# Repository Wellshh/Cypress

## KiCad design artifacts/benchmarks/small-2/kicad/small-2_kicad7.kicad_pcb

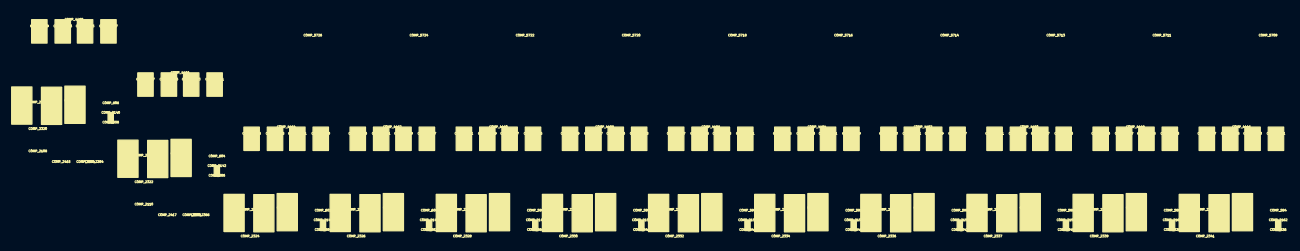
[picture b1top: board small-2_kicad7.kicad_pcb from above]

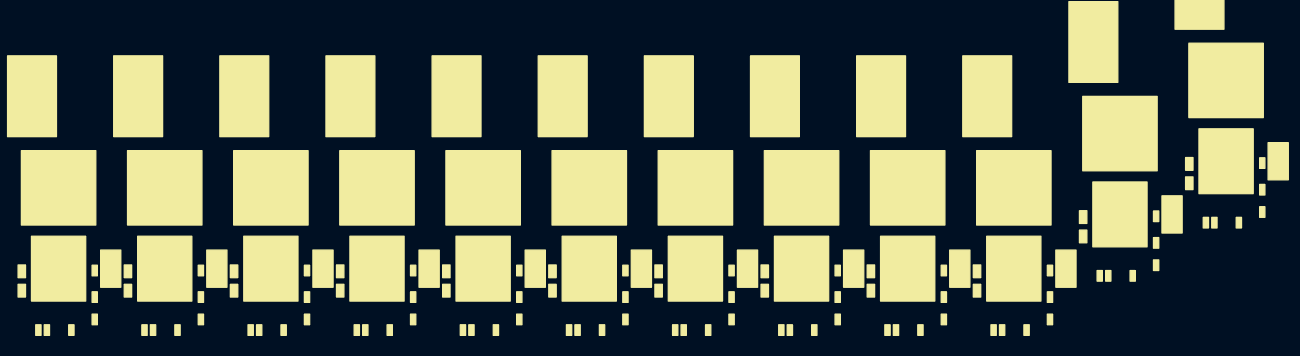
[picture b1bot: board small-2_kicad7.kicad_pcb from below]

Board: 2 copper layers, 240 parts (144 on the bottom side), 88 nets, no tracks yet.

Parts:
COMP_536: COMP_536; 032-1642-000
COMP_538: COMP_538; 032-1642-000
COMP_540: COMP_540; 032-1642-000
COMP_542: COMP_542; 032-1642-000
COMP_544: COMP_544; 032-1642-000
COMP_546: COMP_546; 032-1642-000
COMP_548: COMP_548; 032-1642-000
COMP_550: COMP_550; 032-1642-000
COMP_552: COMP_552; 032-1642-000
COMP_554: COMP_554; 032-1642-000
COMP_556: COMP_556; 032-1642-000
COMP_558: COMP_558; 032-1642-000
COMP_584: COMP_584; 032-1642-000
COMP_586: COMP_586; 032-1642-000
COMP_588: COMP_588; 032-1642-000
COMP_590: COMP_590; 032-1642-000
COMP_592: COMP_592; 032-1642-000
COMP_594: COMP_594; 032-1642-000
COMP_596: COMP_596; 032-1642-000
COMP_598: COMP_598; 032-1642-000
COMP_600: COMP_600; 032-1642-000
COMP_602: COMP_602; 032-1642-000
COMP_604: COMP_604; 032-1642-000
COMP_606: COMP_606; 032-1642-000
COMP_1898: COMP_1898; 032-1468-000
COMP_2108: COMP_2108; 032-1468-000
COMP_2110: COMP_2110; 032-1468-000
COMP_2112: COMP_2112; 032-1468-000
COMP_2114: COMP_2114; 032-1468-000
COMP_2116: COMP_2116; 032-1468-000
COMP_2118: COMP_2118; 032-1468-000
COMP_2120: COMP_2120; 032-1468-000
COMP_2121: COMP_2121; 032-0863-000
COMP_2123: COMP_2123; 032-1468-000
COMP_2125: COMP_2125; 032-1468-000
COMP_2127: COMP_2127; 032-1468-000
COMP_2129: COMP_2129; 032-1468-000
COMP_2140: COMP_2140; 195-3907-000
COMP_2142: COMP_2142; 195-3907-000
COMP_2144: COMP_2144; 195-3907-000
COMP_2146: COMP_2146; 195-3907-000
COMP_2148: COMP_2148; 195-3907-000
COMP_2150: COMP_2150; 195-3907-000
COMP_2152: COMP_2152; 195-3907-000
COMP_2154: COMP_2154; 195-3907-000
COMP_2156: COMP_2156; 195-3907-000
COMP_2158: COMP_2158; 195-3907-000
COMP_2160: COMP_2160; 195-3907-000
COMP_2162: COMP_2162; 195-3907-000
COMP_2184: COMP_2184; 195-3953-000
COMP_2186: COMP_2186; 195-3953-000
COMP_2188: COMP_2188; 195-3953-000
COMP_2190: COMP_2190; 195-3953-000
COMP_2192: COMP_2192; 195-3953-000
COMP_2194: COMP_2194; 195-3953-000
COMP_2196: COMP_2196; 195-3953-000
COMP_2198: COMP_2198; 195-3953-000
COMP_2200: COMP_2200; 195-3953-000
COMP_2202: COMP_2202; 195-3953-000
COMP_2204: COMP_2204; 195-3953-000
COMP_2206: COMP_2206; 195-3953-000
COMP_2288: COMP_2288; 032-0863-000
COMP_2290: COMP_2290; 032-0863-000
COMP_2292: COMP_2292; 032-0863-000
COMP_2296: COMP_2296; 032-0863-000
COMP_2298: COMP_2298; 032-0863-000
COMP_2300: COMP_2300; 032-0863-000
COMP_2302: COMP_2302; 032-0863-000
COMP_2304: COMP_2304; 032-0863-000
COMP_2306: COMP_2306; 032-0863-000
COMP_2308: COMP_2308; 032-0863-000
COMP_2310: COMP_2310; 032-0863-000
COMP_2320: COMP_2320; 032-0863-000
COMP_2322: COMP_2322; 032-0863-000
COMP_2324: COMP_2324; 032-0863-000
COMP_2326: COMP_2326; 032-0863-000
COMP_2328: COMP_2328; 032-0863-000
COMP_2330: COMP_2330; 032-0863-000
COMP_2332: COMP_2332; 032-0863-000
COMP_2334: COMP_2334; 032-0863-000
COMP_2336: COMP_2336; 032-0863-000
COMP_2337: COMP_2337; 032-0863-000
COMP_2339: COMP_2339; 032-0863-000
COMP_2341: COMP_2341; 032-0863-000
COMP_2351: COMP_2351; 195-2655-000
COMP_2384: COMP_2384; 195-2655-000
COMP_2386: COMP_2386; 195-2655-000
COMP_2388: COMP_2388; 195-2655-000
COMP_2390: COMP_2390; 195-2655-000
COMP_2392: COMP_2392; 195-2655-000
COMP_2394: COMP_2394; 195-2655-000
COMP_2396: COMP_2396; 195-2655-000
COMP_2398: COMP_2398; 195-2655-000
COMP_2400: COMP_2400; 195-2655-000
COMP_2402: COMP_2402; 195-2655-000
COMP_2404: COMP_2404; 195-2655-000
COMP_2406: COMP_2406; 195-2655-000
COMP_2407: COMP_2407; 195-2655-000
COMP_2415: COMP_2415; 195-2655-000
COMP_2417: COMP_2417; 195-2655-000
COMP_2419: COMP_2419; 195-2655-000
COMP_2421: COMP_2421; 195-2655-000
COMP_2423: COMP_2423; 195-2655-000
COMP_2425: COMP_2425; 195-2655-000
COMP_2427: COMP_2427; 195-2655-000
COMP_2429: COMP_2429; 195-2655-000
COMP_2431: COMP_2431; 195-2655-000
COMP_2435: COMP_2435; 195-2655-000
COMP_4062: COMP_4062; 032-2076-000
COMP_4064: COMP_4064; 032-2076-000
COMP_4066: COMP_4066; 032-2076-000
COMP_4068: COMP_4068; 032-2076-000
COMP_4070: COMP_4070; 032-2076-000
COMP_4072: COMP_4072; 032-2076-000
COMP_4074: COMP_4074; 032-2076-000
COMP_4076: COMP_4076; 032-2076-000
COMP_4078: COMP_4078; 032-2076-000
COMP_4080: COMP_4080; 032-2076-000
COMP_4082: COMP_4082; 032-2076-000
COMP_4084: COMP_4084; 032-2076-000
COMP_4094: COMP_4094; 032-2076-000
COMP_4096: COMP_4096; 032-2076-000
COMP_4098: COMP_4098; 032-2076-000
COMP_4100: COMP_4100; 032-2076-000
COMP_4102: COMP_4102; 032-2076-000
COMP_4104: COMP_4104; 032-2076-000
COMP_4106: COMP_4106; 032-2076-000
COMP_4108: COMP_4108; 032-2076-000
COMP_4110: COMP_4110; 032-2076-000
COMP_4112: COMP_4112; 032-2076-000
COMP_4114: COMP_4114; 032-2076-000
COMP_4116: COMP_4116; 032-2076-000
COMP_4126: COMP_4126; 032-2076-000
COMP_4128: COMP_4128; 032-2076-000
COMP_4130: COMP_4130; 032-2076-000
COMP_4132: COMP_4132; 032-2076-000
COMP_4134: COMP_4134; 032-2076-000
COMP_4136: COMP_4136; 032-2076-000
COMP_4138: COMP_4138; 032-2076-000
COMP_4140: COMP_4140; 032-2076-000
COMP_4142: COMP_4142; 032-2076-000
COMP_4144: COMP_4144; 032-2076-000
COMP_4146: COMP_4146; 032-2076-000
COMP_4148: COMP_4148; 032-2076-000
COMP_4158: COMP_4158; 032-2076-000
COMP_4160: COMP_4160; 032-2076-000
COMP_4162: COMP_4162; 032-2076-000
COMP_4164: COMP_4164; 032-2076-000
COMP_4166: COMP_4166; 032-2076-000
COMP_4168: COMP_4168; 032-2076-000
COMP_4170: COMP_4170; 032-2076-000
COMP_4172: COMP_4172; 032-2076-000
COMP_4174: COMP_4174; 032-2076-000
COMP_4176: COMP_4176; 032-2076-000
COMP_4178: COMP_4178; 032-2076-000
COMP_4180: COMP_4180; 032-2076-000
COMP_4308: COMP_4308; 316-0577-000
COMP_4310: COMP_4310; 316-0577-000
COMP_4312: COMP_4312; 316-0577-000
COMP_4314: COMP_4314; 316-0577-000
COMP_4316: COMP_4316; 316-0577-000
COMP_4318: COMP_4318; 316-0577-000
COMP_4320: COMP_4320; 316-0577-000
COMP_4322: COMP_4322; 316-0577-000
COMP_4324: COMP_4324; 316-0577-000
COMP_4326: COMP_4326; 316-0577-000
COMP_4328: COMP_4328; 316-0577-000
COMP_4330: COMP_4330; 316-0577-000
COMP_4446: COMP_4446; 130-1618-000
COMP_4448: COMP_4448; 130-1618-000
COMP_4450: COMP_4450; 130-1618-000
COMP_4452: COMP_4452; 130-1618-000
COMP_4454: COMP_4454; 130-1618-000
COMP_4456: COMP_4456; 130-1618-000
COMP_4458: COMP_4458; 130-1618-000
COMP_4460: COMP_4460; 130-1618-000
COMP_4462: COMP_4462; 130-1618-000
COMP_4464: COMP_4464; 130-1618-000
COMP_4466: COMP_4466; 130-1618-000
COMP_4468: COMP_4468; 130-1618-000
COMP_5321: COMP_5321; 032-0055-000
COMP_5323: COMP_5323; 032-0055-000
COMP_5325: COMP_5325; 032-0055-000
COMP_5327: COMP_5327; 032-0055-000
COMP_5329: COMP_5329; 032-0055-000
COMP_5331: COMP_5331; 032-0055-000
COMP_5333: COMP_5333; 032-0055-000
COMP_5335: COMP_5335; 032-0055-000
COMP_5337: COMP_5337; 032-0055-000
COMP_5339: COMP_5339; 032-0055-000
COMP_5341: COMP_5341; 032-0055-000
COMP_5343: COMP_5343; 032-0055-000
COMP_5353: COMP_5353; 032-0055-000
COMP_5355: COMP_5355; 032-0055-000
COMP_5357: COMP_5357; 032-0055-000
COMP_5359: COMP_5359; 032-0055-000
COMP_5361: COMP_5361; 032-0055-000
COMP_5363: COMP_5363; 032-0055-000
COMP_5365: COMP_5365; 032-0055-000
COMP_5367: COMP_5367; 032-0055-000
COMP_5369: COMP_5369; 032-0055-000
COMP_5371: COMP_5371; 032-0055-000
COMP_5373: COMP_5373; 032-0055-000
COMP_5375: COMP_5375; 032-0055-000
COMP_5385: COMP_5385; 032-0055-000
COMP_5387: COMP_5387; 032-0055-000
COMP_5389: COMP_5389; 032-0055-000
COMP_5391: COMP_5391; 032-0055-000
COMP_5393: COMP_5393; 032-0055-000
COMP_5395: COMP_5395; 032-0055-000
COMP_5397: COMP_5397; 032-0055-000
COMP_5399: COMP_5399; 032-0055-000
COMP_5401: COMP_5401; 032-0055-000
COMP_5403: COMP_5403; 032-0055-000
COMP_5405: COMP_5405; 032-0055-000
COMP_5407: COMP_5407; 032-0055-000
COMP_5417: COMP_5417; 032-0055-000
COMP_5419: COMP_5419; 032-0055-000
COMP_5421: COMP_5421; 032-0055-000
COMP_5423: COMP_5423; 032-0055-000
COMP_5425: COMP_5425; 032-0055-000
COMP_5427: COMP_5427; 032-0055-000
COMP_5429: COMP_5429; 032-0055-000
COMP_5431: COMP_5431; 032-0055-000
COMP_5433: COMP_5433; 032-0055-000
COMP_5435: COMP_5435; 032-0055-000
COMP_5437: COMP_5437; 032-0055-000
COMP_5439: COMP_5439; 032-0055-000
COMP_5709: COMP_5709; 032-1638-000
COMP_5711: COMP_5711; 032-1638-000
COMP_5713: COMP_5713; 032-1638-000
COMP_5714: COMP_5714; 032-1638-000
COMP_5716: COMP_5716; 032-1638-000
COMP_5718: COMP_5718; 032-1638-000
COMP_5720: COMP_5720; 032-1638-000
COMP_5722: COMP_5722; 032-1638-000
COMP_5724: COMP_5724; 032-1638-000
COMP_5726: COMP_5726; 032-1638-000
COMP_5728: COMP_5728; 032-1638-000
COMP_5730: COMP_5730; 032-1638-000

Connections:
NET_10: COMP_2121.1, COMP_2288.1, COMP_2290.1, COMP_2292.1, COMP_2296.1, COMP_2298.1, COMP_2300.1, COMP_2302.1, COMP_2304.1, COMP_2306.1, COMP_2308.1, COMP_2310.1, COMP_2320.1, COMP_2322.1, COMP_2324.1, COMP_2326.1, COMP_2328.1, COMP_2330.1, COMP_2332.1, COMP_2334.1, COMP_2336.1, COMP_2337.1, COMP_2339.1, COMP_2341.1, COMP_4062.1, COMP_4064.1, COMP_4066.1, COMP_4068.1, COMP_4070.1, COMP_4072.1, COMP_4074.1, COMP_4076.1, COMP_4078.1, COMP_4080.1, COMP_4082.1, COMP_4084.1, COMP_4094.1, COMP_4096.1, COMP_4098.1, COMP_4100.1, COMP_4102.1, COMP_4104.1, COMP_4106.1, COMP_4108.1, COMP_4110.1, COMP_4112.1, COMP_4114.1, COMP_4116.1, COMP_4126.1, COMP_4128.1, COMP_4130.1, COMP_4132.1, COMP_4134.1, COMP_4136.1, COMP_4138.1, COMP_4140.1, COMP_4142.1, COMP_4144.1, COMP_4146.1, COMP_4148.1, COMP_4158.1, COMP_4160.1, COMP_4162.1, COMP_4164.1, COMP_4166.1, COMP_4168.1, COMP_4170.1, COMP_4172.1, COMP_4174.1, COMP_4176.1, COMP_4178.1, COMP_4180.1, COMP_4308.25, COMP_4308.30, COMP_4310.25, COMP_4310.30, COMP_4312.25, COMP_4312.30, COMP_4314.25, COMP_4314.30, COMP_4316.25, COMP_4316.30, COMP_4318.25, COMP_4318.30, COMP_4320.25, COMP_4320.30, COMP_4322.25, COMP_4322.30, COMP_4324.25, COMP_4324.30, COMP_4326.25, COMP_4326.30, COMP_4328.25, COMP_4328.30, COMP_4330.25, COMP_4330.30
NET_373: COMP_2108.1, COMP_2415.2
NET_374: COMP_2110.1, COMP_2417.2
NET_375: COMP_2112.1, COMP_2419.2
NET_376: COMP_2114.1, COMP_2421.2
NET_377: COMP_2116.1, COMP_2423.2
NET_378: COMP_2118.1, COMP_2425.2
NET_380: COMP_2120.1, COMP_2427.2
NET_381: COMP_1898.1, COMP_2429.2
NET_382: COMP_2123.1, COMP_2431.2
NET_383: COMP_2127.1, COMP_2407.2
NET_384: COMP_2125.1, COMP_2351.2
NET_385: COMP_2129.1, COMP_2435.2
NET_420: COMP_2415.1, COMP_4308.33
NET_421: COMP_2417.1, COMP_4310.33
NET_422: COMP_2419.1, COMP_4312.33
NET_423: COMP_2421.1, COMP_4314.33
NET_424: COMP_2423.1, COMP_4316.33
NET_425: COMP_2425.1, COMP_4318.33
NET_427: COMP_2427.1, COMP_4320.33
NET_428: COMP_2429.1, COMP_4322.33
NET_429: COMP_2431.1, COMP_4324.33
NET_430: COMP_2407.1, COMP_4328.33
NET_431: COMP_2351.1, COMP_4326.33
NET_432: COMP_2435.1, COMP_4330.33
NET_468: COMP_2108.2, COMP_4308.32
NET_469: COMP_2110.2, COMP_4310.32
NET_470: COMP_2112.2, COMP_4312.32
NET_471: COMP_2114.2, COMP_4314.32
NET_472: COMP_2116.2, COMP_4316.32
NET_473: COMP_2118.2, COMP_4318.32
NET_475: COMP_2120.2, COMP_4320.32
NET_476: COMP_1898.2, COMP_4322.32
NET_477: COMP_2123.2, COMP_4324.32
NET_478: COMP_2127.2, COMP_4328.32
NET_479: COMP_2125.2, COMP_4326.32
NET_480: COMP_2129.2, COMP_4330.32
NET_516: COMP_4308.10, COMP_4308.11, COMP_4308.12, COMP_4308.13, COMP_4308.14, COMP_4308.15, COMP_4308.16, COMP_4308.17, COMP_4308.18, COMP_4308.19, COMP_4468.1
NET_517: COMP_4310.10, COMP_4310.11, COMP_4310.12, COMP_4310.13, COMP_4310.14, COMP_4310.15, COMP_4310.16, COMP_4310.17, COMP_4310.18, COMP_4310.19, COMP_4466.1
NET_518: COMP_4312.10, COMP_4312.11, COMP_4312.12, COMP_4312.13, COMP_4312.14, COMP_4312.15, COMP_4312.16, COMP_4312.17, COMP_4312.18, COMP_4312.19, COMP_4464.1
NET_519: COMP_4314.10, COMP_4314.11, COMP_4314.12, COMP_4314.13, COMP_4314.14, COMP_4314.15, COMP_4314.16, COMP_4314.17, COMP_4314.18, COMP_4314.19, COMP_4462.1
NET_520: COMP_4316.10, COMP_4316.11, COMP_4316.12, COMP_4316.13, COMP_4316.14, COMP_4316.15, COMP_4316.16, COMP_4316.17, COMP_4316.18, COMP_4316.19, COMP_4460.1
NET_521: COMP_4318.10, COMP_4318.11, COMP_4318.12, COMP_4318.13, COMP_4318.14, COMP_4318.15, COMP_4318.16, COMP_4318.17, COMP_4318.18, COMP_4318.19, COMP_4458.1
NET_523: COMP_4320.10, COMP_4320.11, COMP_4320.12, COMP_4320.13, COMP_4320.14, COMP_4320.15, COMP_4320.16, COMP_4320.17, COMP_4320.18, COMP_4320.19, COMP_4456.1
NET_524: COMP_4322.10, COMP_4322.11, COMP_4322.12, COMP_4322.13, COMP_4322.14, COMP_4322.15, COMP_4322.16, COMP_4322.17, COMP_4322.18, COMP_4322.19, COMP_4454.1
NET_525: COMP_4324.10, COMP_4324.11, COMP_4324.12, COMP_4324.13, COMP_4324.14, COMP_4324.15, COMP_4324.16, COMP_4324.17, COMP_4324.18, COMP_4324.19, COMP_4452.1
NET_526: COMP_4328.10, COMP_4328.11, COMP_4328.12, COMP_4328.13, COMP_4328.14, COMP_4328.15, COMP_4328.16, COMP_4328.17, COMP_4328.18, COMP_4328.19, COMP_4448.1
NET_527: COMP_4326.10, COMP_4326.11, COMP_4326.12, COMP_4326.13, COMP_4326.14, COMP_4326.15, COMP_4326.16, COMP_4326.17, COMP_4326.18, COMP_4326.19, COMP_4450.1
NET_528: COMP_4330.10, COMP_4330.11, COMP_4330.12, COMP_4330.13, COMP_4330.14, COMP_4330.15, COMP_4330.16, COMP_4330.17, COMP_4330.18, COMP_4330.19, COMP_4446.1
NET_5240: COMP_2184.2, COMP_4308.35
NET_5241: COMP_2186.2, COMP_4310.35
NET_5242: COMP_2188.2, COMP_4312.35
NET_5243: COMP_2190.2, COMP_4314.35
NET_5244: COMP_2192.2, COMP_4316.35
NET_5245: COMP_2194.2, COMP_4318.35
NET_5247: COMP_2196.2, COMP_4320.35
NET_5248: COMP_2198.2, COMP_4322.35
NET_5249: COMP_2200.2, COMP_4324.35
NET_5250: COMP_2204.2, COMP_4328.35
NET_5251: COMP_2202.2, COMP_4326.35
NET_5252: COMP_2206.2, COMP_4330.35
NET_5288: COMP_2384.2, COMP_4308.36
NET_5289: COMP_2386.2, COMP_4310.36
NET_5290: COMP_2388.2, COMP_4312.36
NET_5291: COMP_2390.2, COMP_4314.36
NET_5292: COMP_2392.2, COMP_4316.36
NET_5293: COMP_2394.2, COMP_4318.36
NET_5295: COMP_2396.2, COMP_4320.36
NET_5296: COMP_2398.2, COMP_4322.36
NET_5297: COMP_2400.2, COMP_4324.36
NET_5298: COMP_2404.2, COMP_4328.36
NET_5299: COMP_2402.2, COMP_4326.36
NET_5300: COMP_2406.2, COMP_4330.36
NET_5336: COMP_558.1, COMP_2140.2, COMP_2184.1, COMP_4308.3
NET_5337: COMP_556.1, COMP_2142.2, COMP_2186.1, COMP_4310.3
NET_5338: COMP_554.1, COMP_2144.2, COMP_2188.1, COMP_4312.3
NET_5339: COMP_552.1, COMP_2146.2, COMP_2190.1, COMP_4314.3
NET_5340: COMP_550.1, COMP_2148.2, COMP_2192.1, COMP_4316.3
NET_5341: COMP_548.1, COMP_2150.2, COMP_2194.1, COMP_4318.3
NET_5343: COMP_546.1, COMP_2152.2, COMP_2196.1, COMP_4320.3
NET_5344: COMP_544.1, COMP_2154.2, COMP_2198.1, COMP_4322.3
NET_5345: COMP_542.1, COMP_2156.2, COMP_2200.1, COMP_4324.3
NET_5346: COMP_538.1, COMP_2160.2, COMP_2204.1, COMP_4328.3
NET_5347: COMP_540.1, COMP_2158.2, COMP_2202.1, COMP_4326.3
NET_5348: COMP_536.1, COMP_2162.2, COMP_2206.1, COMP_4330.3
NET_5522: COMP_2384.1, COMP_2386.1, COMP_2388.1, COMP_2390.1, COMP_2392.1, COMP_2394.1, COMP_2396.1, COMP_2398.1, COMP_2400.1, COMP_2402.1, COMP_2404.1, COMP_2406.1
NET_5566: COMP_4446.2, COMP_4448.2, COMP_4450.2, COMP_4452.2, COMP_4454.2, COMP_4456.2, COMP_4458.2, COMP_4460.2, COMP_4462.2, COMP_4464.2, COMP_4466.2, COMP_4468.2, COMP_5321.1, COMP_5323.1, COMP_5325.1, COMP_5327.1, COMP_5329.1, COMP_5331.1, COMP_5333.1, COMP_5335.1, COMP_5337.1, COMP_5339.1, COMP_5341.1, COMP_5343.1, COMP_5353.1, COMP_5355.1, COMP_5357.1, COMP_5359.1, COMP_5361.1, COMP_5363.1, COMP_5365.1, COMP_5367.1, COMP_5369.1, COMP_5371.1, COMP_5373.1, COMP_5375.1, COMP_5385.1, COMP_5387.1, COMP_5389.1, COMP_5391.1, COMP_5393.1, COMP_5395.1, COMP_5397.1, COMP_5399.1, COMP_5401.1, COMP_5403.1, COMP_5405.1, COMP_5407.1, COMP_5417.1, COMP_5419.1, COMP_5421.1, COMP_5423.1, COMP_5425.1, COMP_5427.1, COMP_5429.1, COMP_5431.1, COMP_5433.1, COMP_5435.1, COMP_5437.1, COMP_5439.1, COMP_5709.1, COMP_5711.1, COMP_5713.1, COMP_5714.1, COMP_5716.1, COMP_5718.1, COMP_5720.1, COMP_5722.1, COMP_5724.1, COMP_5726.1, COMP_5728.1, COMP_5730.1
NET_5567: COMP_584.1, COMP_586.1, COMP_588.1, COMP_590.1, COMP_592.1, COMP_594.1, COMP_596.1, COMP_598.1, COMP_600.1, COMP_602.1, COMP_604.1, COMP_606.1, COMP_2140.1, COMP_2142.1, COMP_2144.1, COMP_2146.1, COMP_2148.1, COMP_2150.1, COMP_2152.1, COMP_2154.1, COMP_2156.1, COMP_2158.1, COMP_2160.1, COMP_2162.1, COMP_4308.4, COMP_4310.4, COMP_4312.4, COMP_4314.4, COMP_4316.4, COMP_4318.4, COMP_4320.4, COMP_4322.4, COMP_4324.4, COMP_4326.4, COMP_4328.4, COMP_4330.4

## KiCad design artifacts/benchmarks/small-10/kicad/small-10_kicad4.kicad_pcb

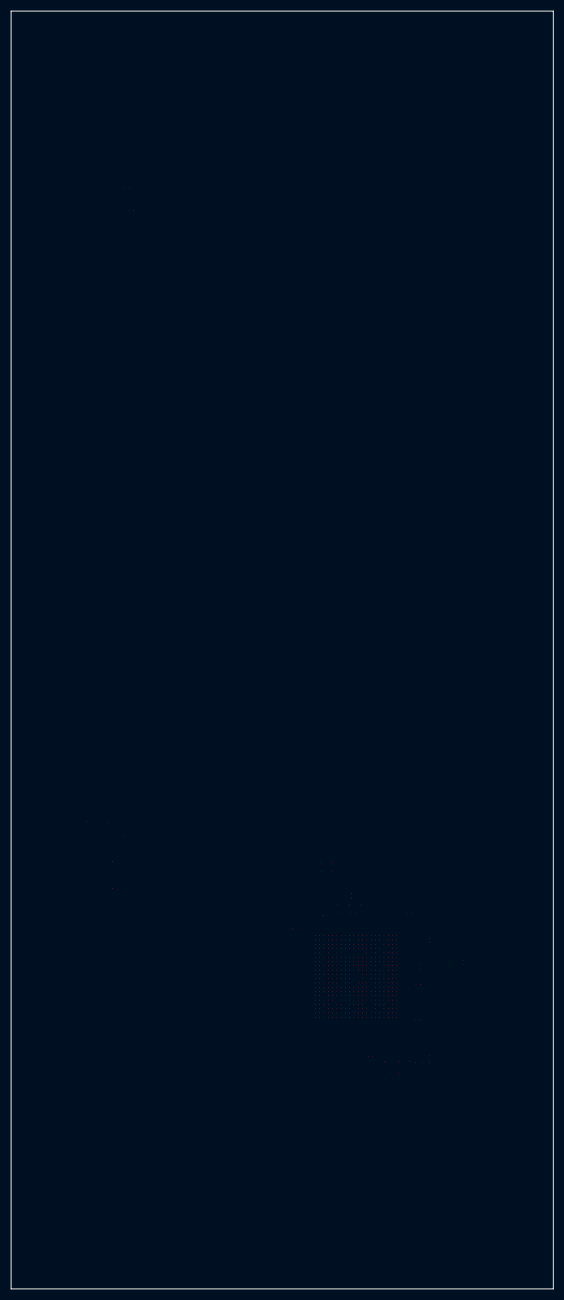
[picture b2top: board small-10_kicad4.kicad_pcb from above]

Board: 2 copper layers, 101.2 x 238.5 mm, 136 parts (0 on the bottom side), 94 nets, no tracks yet.

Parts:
C0: C0; 080-1776-000
C1: C1; 086-0351-000
C2: C2; 080-1982-000
C3: C3; 092-0256-000
C4: C4; 092-0256-000
C5: C5; 100-0274-000
C6: C6; 100-0274-000
C7: C7; 100-0269-000
C8: C8; 032-1563-000
C9: C9; 032-1641-000
C10: C10; 032-1563-000
C11: C11; 032-1563-000
C12: C12; 032-1641-000
C13: C13; 032-0253-000
C14: C14; 032-0253-000
C15: C15; 039-0135-000
C16: C16; 039-0135-000
C17: C17; 195-0167-000
C18: C18; 195-0167-000
C19: C19; 195-0167-000
C20: C20; 032-0863-000
C21: C21; 032-0863-000
C22: C22; 032-0863-000
C23: C23; 032-0863-000
C24: C24; 032-0863-000
C25: C25; 032-0863-000
C26: C26; 032-0863-000
C27: C27; 032-0863-000
C28: C28; 032-0863-000
C29: C29; 032-0863-000
C30: C30; 032-0863-000
C31: C31; 032-0863-000
C32: C32; 032-0863-000
C33: C33; 195-2655-000
C34: C34; 195-2655-000
C35: C35; 195-2655-000
C36: C36; 195-2655-000
C37: C37; 195-2655-000
C38: C38; 195-2655-000
C39: C39; 195-0167-000
C40: C40; 195-0167-000
C41: C41; 195-2655-000
C42: C42; 195-2655-000
C43: C43; 195-2655-000
C44: C44; 195-2655-000
C45: C45; 195-0167-000
C46: C46; 195-0167-000
C47: C47; 195-0167-000
C48: C48; 195-3953-000
C49: C49; 195-3953-000
C50: C50; 195-3953-000
C51: C51; 195-2655-000
C52: C52; 195-2655-000
C53: C53; 195-0167-000
C54: C54; 195-3953-000
C55: C55; 195-3953-000
C56: C56; 195-3953-000
C57: C57; 195-0128-000
C58: C58; 195-3953-000
C59: C59; 195-0167-000
C60: C60; 195-3953-000
C61: C61; 195-0167-000
C62: C62; 195-2655-000
C63: C63; 195-0167-000
C64: C64; 195-0167-000
C65: C65; 195-0167-000
C66: C66; 195-2655-000
C67: C67; 195-0128-000
C68: C68; 195-0128-000
C69: C69; 195-2655-000
C70: C70; 195-2655-000
C71: C71; 195-2655-000
C72: C72; 195-0252-000
C73: C73; 195-0252-000
C74: C74; 195-3953-000
C75: C75; 195-0167-000
C76: C76; 195-0003-000
C77: C77; 195-0252-000
C78: C78; 195-2655-000
C79: C79; 195-0252-000
C80: C80; 195-0252-000
C81: C81; 195-0005-000
C82: C82; 195-3953-000
C83: C83; 195-0167-000
C84: C84; 195-3953-000
C85: C85; 195-0003-000
C86: C86; 195-0252-000
C87: C87; 195-3953-000
C88: C88; 032-0863-000
C89: C89; 032-0863-000
C90: C90; 032-0863-000
C91: C91; 032-0863-000
C92: C92; 032-0863-000
C93: C93; 032-0863-000
C94: C94; 195-3953-000
C95: C95; 195-3953-000
C96: C96; 195-0167-000
C97: C97; 195-0167-000
C98: C98; 195-0167-000
C99: C99; 195-0252-000
C100: C100; 195-3953-000
C101: C101; 032-0863-000
C102: C102; 032-0863-000
C103: C103; 032-0863-000
C104: C104; 032-0863-000
C105: C105; 032-0863-000
C106: C106; 032-0863-000
C107: C107; 032-0863-000
C108: C108; 032-0863-000
C109: C109; 032-0863-000
C110: C110; 195-3953-000
C111: C111; 032-0863-000
C112: C112; 195-3953-000
C113: C113; 195-2655-000
C114: C114; 195-2655-000
C115: C115; 195-2655-000
C116: C116; 032-0863-000
C117: C117; 195-0167-000
C118: C118; 195-0167-000
C119: C119; 195-3953-000
C120: C120; 195-0167-000
C121: C121; 195-2655-000
C122: C122; 195-0167-000
C123: C123; 195-3953-000
C124: C124; 195-0167-000
C125: C125; 195-0167-000
C126: C126; 032-0863-000
C127: C127; 195-0167-000
C128: C128; 195-2655-000
C129: C129; 195-0167-000
C130: C130; 195-3953-000
C131: C131; 195-3953-000
C132: C132; 195-3953-000
C133: C133; 032-0863-000
C134: C134; 195-2655-000
C135: C135; 115-2974-000

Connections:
NET_0: C6.2, C12.1, C101.1, C116.1, C135.J7, C135.J8
NET_19: C6.1, C11.1, C14.1, C126.1
NET_20: C5.2, C9.1, C20.1, C21.1, C22.1, C23.1, C24.1, C25.1, C26.1, C27.1, C28.1, C29.1, C30.1, C31.1, C32.1, C88.1, C89.1, C90.1, C91.1, C92.1, C93.1, C102.1, C103.1, C104.1, C105.1, C106.1, C107.1, C108.1, C109.1, C135.H8, C135.H9, C135.H10, C135.H11, C135.H12, C135.H13, C135.J9, C135.J10, C135.J11, C135.J12, C135.J13, C135.K8, C135.K9, C135.K12, C135.K13, C135.L9, C135.L12, C135.L13, C135.M8, C135.M9, C135.M10, C135.M12, C135.M13, C135.N8, C135.N9, C135.N10, C135.N11, C135.N12, C135.N13
NET_218: C2.1, C2.3, C3.A, C4.A, C5.1, C7.1, C10.1, C13.1, C16.1, C60.1, C74.1, C81.1, C84.1, C87.1, C94.1, C95.1, C100.1, C111.1, C131.1
NET_466: C114.2, C135.U19
NET_468: C115.1, C135.W18
NET_470: C113.2, C135.T18
NET_472: C121.2, C135.U18
NET_707: C58.1, C135.A13
NET_717: C62.1, C135.P1
NET_720: C44.1, C135.U4
NET_728: C134.2, C135.F13
NET_731: C43.2, C135.G13
NET_743: C70.2, C135.B11
NET_746: C78.2, C135.N5
NET_1030: C112.1, C135.A7
NET_1031: C123.1, C135.A8
NET_1032: C119.1, C135.A9
NET_1033: C110.1, C135.J15
NET_1034: C130.1, C135.H14
NET_1035: C82.1, C135.Y13
NET_1036: C132.1, C135.R1
NET_1037: C49.1, C135.H15
NET_1038: C48.1, C135.C19
NET_1123: C42.1, C135.J4
NET_1125: C41.1, C135.J3
NET_1148: C57.1, C135.E14
NET_1149: C2.2, C56.1, C57.2
NET_1155: C0.1, C84.2, C135.E15
NET_1156: C0.3, C95.2, C135.D15
NET_1160: C118.2, C135.D1
NET_3366: C69.2, C135.C3
NET_3368: C66.2, C135.C4
NET_3801: C87.2, C135.C13
NET_3802: C94.2, C135.Y20
NET_3803: C74.2, C135.A19
NET_3804: C8.1, C81.2, C135.C17
NET_3805: C100.2, C135.D13
NET_3852: C68.2, C135.A17
NET_3853: C4.K, C68.1
NET_3854: C67.2, C135.A18
NET_3855: C3.K, C67.1
NET_4565: C40.1, C135.W16
NET_4568: C33.2, C135.T10
NET_4571: C37.2, C135.P16
NET_4573: C39.2, C135.P9
NET_4576: C34.1, C135.F10
NET_4579: C38.2, C135.D11
NET_4586: C77.2, C135.T2
NET_4587: C72.1, C135.T3
NET_4588: C73.1, C135.V1
NET_4589: C99.1, C135.V2
NET_4590: C97.2, C135.U1
NET_4591: C86.2, C135.T1
NET_4592: C80.2, C135.U2
NET_4593: C1.1, C131.2
NET_4615: C124.2, C135.W9
NET_4616: C1.3, C124.1
NET_4666: C19.2, C135.J2
NET_4668: C18.2, C135.J1
NET_4670: C17.2, C135.L4
NET_4674: C117.2, C135.K2
NET_4676: C64.2, C135.K1
NET_4678: C47.2, C135.K6
NET_4682: C98.2, C135.K4
NET_4694: C128.2, C135.K5
NET_4708: C79.2, C135.L3
NET_4710: C83.1, C135.E19
NET_4712: C120.1, C135.D20
NET_4714: C127.1, C135.R3
NET_4716: C65.1, C135.R4
NET_4718: C45.1, C135.J19
NET_4720: C46.1, C135.L17
NET_4731: C122.1, C135.D6
NET_4733: C75.2, C135.Y4
NET_6414: C125.2, C135.G5
NET_6416: C129.1, C135.G4
NET_6424: C71.1, C135.A3
NET_6427: C36.1, C135.F7
NET_6430: C51.1, C135.G7
NET_6443: C63.1, C135.R12
NET_6445: C35.2, C135.G12
NET_6448: C52.2, C135.F14
NET_6461: C61.1, C135.P12
NET_6462: C59.1, C135.G3
NET_6465: C96.2, C135.Y3
NET_6527: C85.1, C135.V3
NET_6530: C54.1, C135.F15
NET_6531: C55.1, C135.A20
NET_6532: C50.1, C135.B20
NET_6576: C60.2, C135.A2
NET_6739: C53.1, C135.H1
NET_6882: C76.1, C135.G19
NET_6946: C1.4, C7.2, C15.1, C133.1

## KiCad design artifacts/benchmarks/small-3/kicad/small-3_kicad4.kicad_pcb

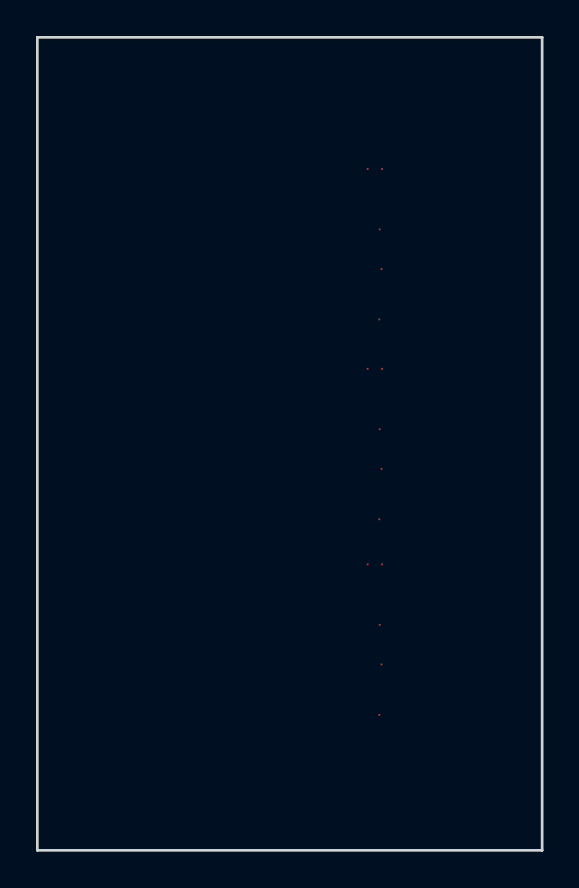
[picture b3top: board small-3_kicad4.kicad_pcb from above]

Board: 2 copper layers, 28.0 x 45.2 mm, 63 parts (0 on the bottom side), 26 nets, no tracks yet.

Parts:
C0: C0; 032-1642-000
C1: C1; 032-1642-000
C2: C2; 032-1642-000
C3: C3; 032-1642-000
C4: C4; 032-1642-000
C5: C5; 032-1642-000
C6: C6; 032-1468-000
C7: C7; 032-1468-000
C8: C8; 032-1468-000
C9: C9; 195-3907-000
C10: C10; 195-3907-000
C11: C11; 195-3907-000
C12: C12; 195-3953-000
C13: C13; 195-3953-000
C14: C14; 195-3953-000
C15: C15; 032-0863-000
C16: C16; 032-0863-000
C17: C17; 032-0863-000
C18: C18; 032-0863-000
C19: C19; 032-0863-000
C20: C20; 032-0863-000
C21: C21; 195-2655-000
C22: C22; 195-2655-000
C23: C23; 195-2655-000
C24: C24; 195-2655-000
C25: C25; 195-2655-000
C26: C26; 195-2655-000
C27: C27; 032-2076-000
C28: C28; 032-2076-000
C29: C29; 032-2076-000
C30: C30; 032-2076-000
C31: C31; 032-2076-000
C32: C32; 032-2076-000
C33: C33; 032-2076-000
C34: C34; 032-2076-000
C35: C35; 032-2076-000
C36: C36; 032-2076-000
C37: C37; 032-2076-000
C38: C38; 032-2076-000
C39: C39; 130-1566-000
C40: C40; 130-1566-000
C41: C41; 130-1566-000
C42: C42; 316-0577-000
C43: C43; 316-0577-000
C44: C44; 316-0577-000
C45: C45; 032-1721-000
C46: C46; 032-1721-000
C47: C47; 032-1721-000
C48: C48; 032-1721-000
C49: C49; 032-1721-000
C50: C50; 032-1721-000
C51: C51; 032-1721-000
C52: C52; 032-1721-000
C53: C53; 032-1721-000
C54: C54; 032-1721-000
C55: C55; 032-1721-000
C56: C56; 032-1721-000
C57: C57; 032-1721-000
C58: C58; 032-1721-000
C59: C59; 032-1721-000
C60: C60; 032-1721-000
C61: C61; 032-1721-000
C62: C62; 032-1721-000

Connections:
NET_6: C15.1, C16.1, C17.1, C18.1, C19.1, C20.1, C27.1, C28.1, C29.1, C30.1, C31.1, C32.1, C33.1, C34.1, C35.1, C36.1, C37.1, C38.1, C42.25, C42.30, C43.25, C43.30, C44.25, C44.30
NET_396: C8.1, C26.2
NET_397: C7.1, C25.2
NET_398: C6.1, C24.2
NET_443: C26.1, C44.33
NET_444: C25.1, C43.33
NET_445: C24.1, C42.33
NET_491: C8.2, C44.32
NET_492: C7.2, C43.32
NET_493: C6.2, C42.32
NET_539: C39.1, C44.10, C44.11, C44.12, C44.13, C44.14, C44.15, C44.16, C44.17, C44.18, C44.19
NET_540: C40.1, C43.10, C43.11, C43.12, C43.13, C43.14, C43.15, C43.16, C43.17, C43.18, C43.19
NET_541: C41.1, C42.10, C42.11, C42.12, C42.13, C42.14, C42.15, C42.16, C42.17, C42.18, C42.19
NET_650: C39.2, C45.1, C48.1, C51.1, C54.1, C57.1, C60.1
NET_2431: C40.2, C41.2, C46.1, C47.1, C49.1, C50.1, C52.1, C53.1, C55.1, C56.1, C58.1, C59.1, C61.1, C62.1
NET_5136: C21.1, C22.1
NET_5263: C14.2, C44.35
NET_5264: C13.2, C43.35
NET_5265: C12.2, C42.35
NET_5311: C23.2, C44.36
NET_5312: C22.2, C43.36
NET_5313: C21.2, C42.36
NET_5359: C0.1, C11.2, C14.1, C44.3
NET_5360: C1.1, C10.2, C13.1, C43.3
NET_5361: C2.1, C9.2, C12.1, C42.3
NET_5567: C3.1, C4.1, C5.1, C9.1, C10.1, C11.1, C42.4, C43.4, C44.4

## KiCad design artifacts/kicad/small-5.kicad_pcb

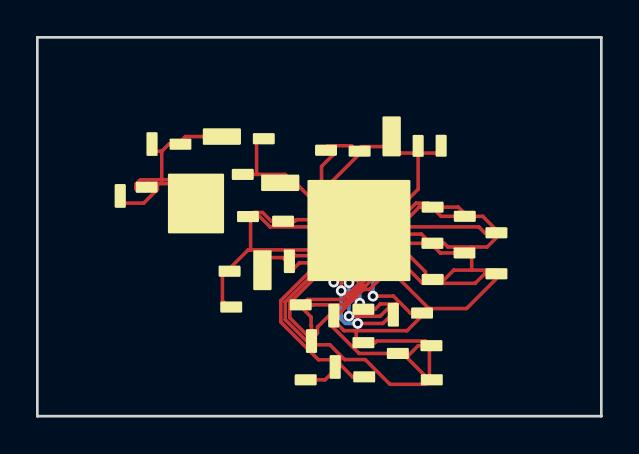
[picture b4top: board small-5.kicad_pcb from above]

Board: 2 copper layers, 31.3 x 21.0 mm, 41 parts (0 on the bottom side), 29 nets.

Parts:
C3049: C3049
C3050: C3050
C3051: C3051
C3053: C3053
C3054: C3054
C3055: C3055
C3056: C3056
C3057: C3057
C3058: C3058
C3059: C3059
R2997: R2997
R2998: R2998
R3002: R3002
R3003: R3003
R3004: R3004
R3005: R3005
R3007: R3007
R3008: R3008
R3009: R3009
R3010: R3010
R3011: R3011
R3012: R3012
R3013: R3013
R3014: R3014
R3015: R3015
R3016: R3016
R3017: R3017
R3018: R3018
R3019: R3019
R3020: R3020
R3021: R3021
R3022: R3022
R3023: R3023
R3024: R3024
R3025: R3025
R3026: R3026
R3028: R3028
R3029: R3029
R3031: R3031
U374: U374
U400: U400

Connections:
GP_DCDC_VCORE_CPLD_ALERT: R3004.1, U400.11
GP_DCDC_VCORE_PSI: R3007.0, U400.12
GP_VCORE_CSSUM: R3017.0, R3018.0, R3019.0, R3020.0, R3021.0, R3022.0, R3023.0, R3024.0, R3025.0, R3026.0, U400.14
GP_VCORE_IREF: R3013.0, U400.15
GP_VCORE_REF_ADJ: C3059.0, R3029.0, U374.0
GP_VCORE_VDIFF: R3002.0, U400.16
GP_VCORE_VFB: R3002.1, U400.17
GP_VCORE_VR_IMON_R: R3011.0, R3012.0
NET_3.3V_CONT_VCORE: C3049.0, C3051.0, R2997.1, R3004.0, R3005.0, U400.0
S_ADDR_PMBUS_CONT_VCORE: R3009.0, R3010.0, U400.21
S_TAO_VCORE_R: C3050.0, R2998.1, R3003.0, U400.22
S_VCORE_ACSP1_P: R3026.1, U400.24
S_VCORE_ACSP2_P: R3025.1, U400.25
S_VCORE_ACSP3_P: R3024.1, U400.26
S_VCORE_ACSP4_P: R3023.1, U400.27
S_VCORE_ACSP5_P: R3022.1, U400.28
S_VCORE_ACSP6_P: R3021.1, U400.29
S_VCORE_ACSP7_P: R3020.1, U400.30
S_VCORE_ACSP8_P: R3019.1, U400.31
S_VCORE_ACSP9_P: R3018.1, U400.32
S_VCORE_ACSP10_P: R3017.1, U400.23
S_VCORE_EN: R3008.0, U400.33
S_VCORE_PG: R3005.1, U400.34
S_VCORE_SENSE_N: C3057.0, U400.35
S_VCORE_SENSE_P_R: C3057.1, R3016.1, U400.36
S_VCORE_VR_IMON: C3053.0, R3011.1, U400.37
S_VINSEN_VCORE: C3056.0, R3014.1, R3015.0, U400.38
S_VREF_REFOUT_VCORE: C3058.0, R3028.1, R3029.1, R3031.1, U374.1
S_VREF_VDD18_VCORE: C3054.0, C3055.0, R3007.1, R3009.1, U400.39

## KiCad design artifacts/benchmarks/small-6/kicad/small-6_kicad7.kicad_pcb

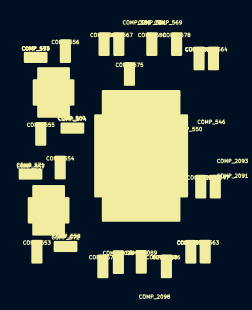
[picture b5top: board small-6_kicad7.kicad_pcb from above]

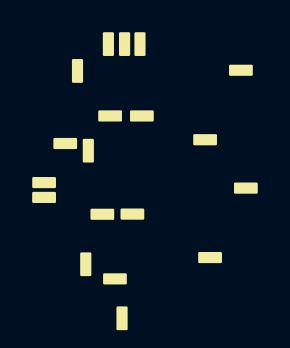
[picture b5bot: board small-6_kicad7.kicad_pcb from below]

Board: 2 copper layers, 46 parts (20 on the bottom side), 22 nets, no tracks yet.

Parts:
COMP_545: COMP_545; 195-2655-000
COMP_546: COMP_546; 195-2655-000
COMP_547: COMP_547; 195-2655-000
COMP_548: COMP_548; 195-2655-000
COMP_549: COMP_549; 036-0022-000
COMP_550: COMP_550; 036-0022-000
COMP_551: COMP_551; 036-0022-000
COMP_552: COMP_552; 036-0022-000
COMP_553: COMP_553; 195-3953-000
COMP_554: COMP_554; 195-3953-000
COMP_555: COMP_555; 195-3953-000
COMP_556: COMP_556; 195-3953-000
COMP_557: COMP_557; 195-0003-000
COMP_558: COMP_558; 195-0003-000
COMP_559: COMP_559; 195-0003-000
COMP_560: COMP_560; 195-0003-000
COMP_561: COMP_561; 195-0233-000
COMP_562: COMP_562; 195-0233-000
COMP_563: COMP_563; 195-3939-000
COMP_564: COMP_564; 196-0045-000
COMP_565: COMP_565; 196-0045-000
COMP_566: COMP_566; 195-0090-000
COMP_567: COMP_567; 195-0090-000
COMP_568: COMP_568; 195-0035-000
COMP_569: COMP_569; 195-0185-000
COMP_570: COMP_570; 195-0185-000
COMP_571: COMP_571; 036-0022-000
COMP_572: COMP_572; 036-0022-000
COMP_573: COMP_573; 036-0022-000
COMP_574: COMP_574; 036-0022-000
COMP_575: COMP_575; 032-0863-000
COMP_576: COMP_576; 195-0295-000
COMP_577: COMP_577; 195-2655-000
COMP_578: COMP_578; 195-4010-000
COMP_579: COMP_579; 195-3372-000
COMP_580: COMP_580; 195-4010-000
COMP_2088: COMP_2088; 196-0073-000
COMP_2089: COMP_2089; 195-0151-000
COMP_2090: COMP_2090; 195-1302-000
COMP_2091: COMP_2091; 195-0364-000
COMP_2093: COMP_2093; 195-0090-000
COMP_2098: COMP_2098; 195-0295-000
COMP_2099: COMP_2099; 195-0295-000
COMP_2272: COMP_2272; 305-0058-000
COMP_2273: COMP_2273; 305-0058-000
COMP_2887: COMP_2887; 115-3132-000

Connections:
NET_5: COMP_547.1, COMP_551.1, COMP_2887.8
NET_35: COMP_545.1, COMP_549.1, COMP_2887.4
NET_39: COMP_546.1, COMP_550.1, COMP_2887.6
NET_49: COMP_553.1, COMP_554.1, COMP_555.1, COMP_556.1, COMP_557.1, COMP_558.1, COMP_559.1, COMP_560.1, COMP_563.1, COMP_564.1, COMP_565.1, COMP_575.1, COMP_2088.1, COMP_2887.3
NET_347: COMP_576.2, COMP_579.1
NET_349: COMP_563.2, COMP_568.2, COMP_576.1, COMP_2887.9
NET_350: COMP_548.2, COMP_552.1, COMP_2887.10
NET_351: COMP_548.1, COMP_2091.2, COMP_2093.1
NET_352: COMP_2089.2, COMP_2099.1
NET_354: COMP_2088.2, COMP_2089.1, COMP_2098.2, COMP_2887.11
NET_355: COMP_567.1, COMP_580.2
NET_357: COMP_561.2, COMP_565.2, COMP_580.1, COMP_2887.5
NET_358: COMP_566.1, COMP_578.2
NET_360: COMP_562.2, COMP_564.2, COMP_578.1, COMP_2887.7
NET_3926: COMP_554.2, COMP_2272.3
NET_3927: COMP_558.2, COMP_572.1, COMP_579.2, COMP_2272.5, COMP_2887.14
NET_3930: COMP_553.2, COMP_2272.6
NET_3931: COMP_557.2, COMP_571.1, COMP_2099.2, COMP_2272.2, COMP_2887.13
NET_3934: COMP_556.2, COMP_2273.3
NET_3935: COMP_560.2, COMP_567.2, COMP_574.1, COMP_2273.5, COMP_2887.2
NET_3936: COMP_555.2, COMP_2273.6
NET_3937: COMP_559.2, COMP_566.2, COMP_573.1, COMP_2273.2, COMP_2887.1

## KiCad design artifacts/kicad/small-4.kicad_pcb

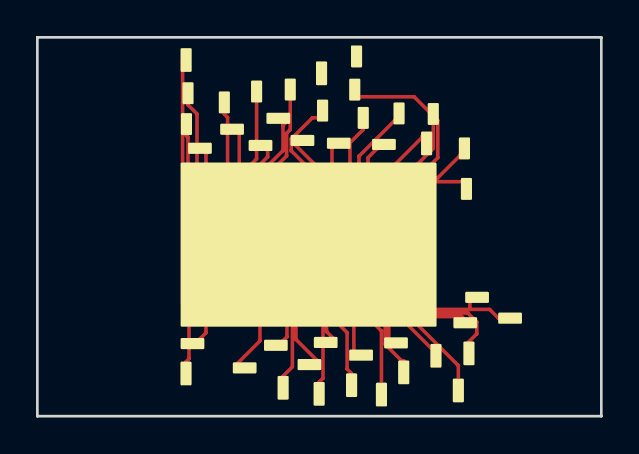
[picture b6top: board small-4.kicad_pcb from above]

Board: 2 copper layers, 31.3 x 21.0 mm, 43 parts (0 on the bottom side), 38 nets.

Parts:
C3019: C3019
C3020: C3020
R1292: R1292
R2256: R2256
R2257: R2257
R2258: R2258
R2637: R2637
R2638: R2638
R2639: R2639
R2758: R2758
R2760: R2760
R2761: R2761
R2763: R2763
R2764: R2764
R2765: R2765
R2766: R2766
R2767: R2767
R2768: R2768
R2769: R2769
R2770: R2770
R2771: R2771
R2772: R2772
R2773: R2773
R2777: R2777
R2778: R2778
R2779: R2779
R2780: R2780
R2782: R2782
R2783: R2783
R2785: R2785
R2786: R2786
R2787: R2787
R2789: R2789
R2792: R2792
R2794: R2794
R2795: R2795
R2796: R2796
R2797: R2797
R2799: R2799
R2800: R2800
R3151: R3151
R4054: R4054
U360: U360

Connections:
AD_0_I2C_AUX: R2761.1, U360.2
AD_1_I2C_AUX: R2760.0, U360.3
AD_2_I2C_AUX: R2758.0, U360.4
GP_ASIC_FU_EN_L_R: R2786.1, U360.5
GP_CEX_FU_EN_L_R: R2785.1, U360.6
GP_GPIO_CPLD_CON_BUF_EN_L_R: R3151.1, U360.7
GP_GPIO_OE_L_R: R2765.1, R2767.0, U360.8
GP_GPIO_RESET_L_R: R2764.1, R2766.1, U360.9
GP_I2C_DCDC_SW_EN_R: R2792.1, U360.11
GP_I2C_TESTING_CON_EN_R: R4054.1, U360.12
GP_I2C_TESTING_S2S_EN_R: R2799.1, U360.13
GP_SECURED_DIS_JUMPER_GPIO_R: R2795.1, U360.14
GP_SPI_COMEX_BURN_EN_L_R: R2789.1, U360.15
GP_SPI_FW_BUF_EN_L_R: R2257.1, U360.16
GP_SPI_FW_BURN_EN_L_R: R2256.1, U360.17
GP_SPI_FW_BURN_SEL_R: R2258.1, U360.18
GP_SPI_FW_MUX_SEL_3.3V_SSD_EN: R2787.1, U360.19
GP_STRAP_FLASH_PRESENT_EN_R: R2639.0, U360.20
I2C_TESTING_GPIO_SCL: R2763.1, U360.21
I2C_TESTING_GPIO_SDA: R1292.1, U360.22
L_ASIC_CON_JTAG_BUF_EN_L_R: R2800.1, U360.23
L_SOC_JTAG_BUF_EN_R: R2638.1, U360.25
S_1.8V_ASIC_QPS_PWR_EN_R: R2777.1, U360.28
S_2.5V_OSC_EAST_WEST_EN_R: R2797.1, U360.29
S_3.3V_ASIC_EN_R: R2772.1, U360.30
S_3.3V_SSD_PWR_EN_R: R2778.1, U360.31
S_5V_DRV_PWR_EN_R: R2773.1, U360.33
S_ASIC_RCLK_EN_R: R2783.1, U360.36
S_ASIC_RST_L_R: R2782.1, U360.37
S_ASIC_TCXO_EN_R: R2796.1, U360.38
S_CPLD_CEX_PWR_OK_R: R2794.1, U360.41
S_DVDD_0.9V_EAST_EN_R: R2770.1, U360.42
S_DVDD_0.9V_WEST_EN_R: R2771.1, U360.43
S_HVDD_1.2V_EAST_EN_R: R2637.1, U360.44
S_HVDD_1.2V_WEST_EN_R: R2769.1, U360.45
S_PORTS_P01_P16_EN_R: R2780.1, U360.47
S_PORTS_P17_P32_EN_R: R2779.1, U360.48
S_VCORE_EN_R: R2768.1, U360.49
